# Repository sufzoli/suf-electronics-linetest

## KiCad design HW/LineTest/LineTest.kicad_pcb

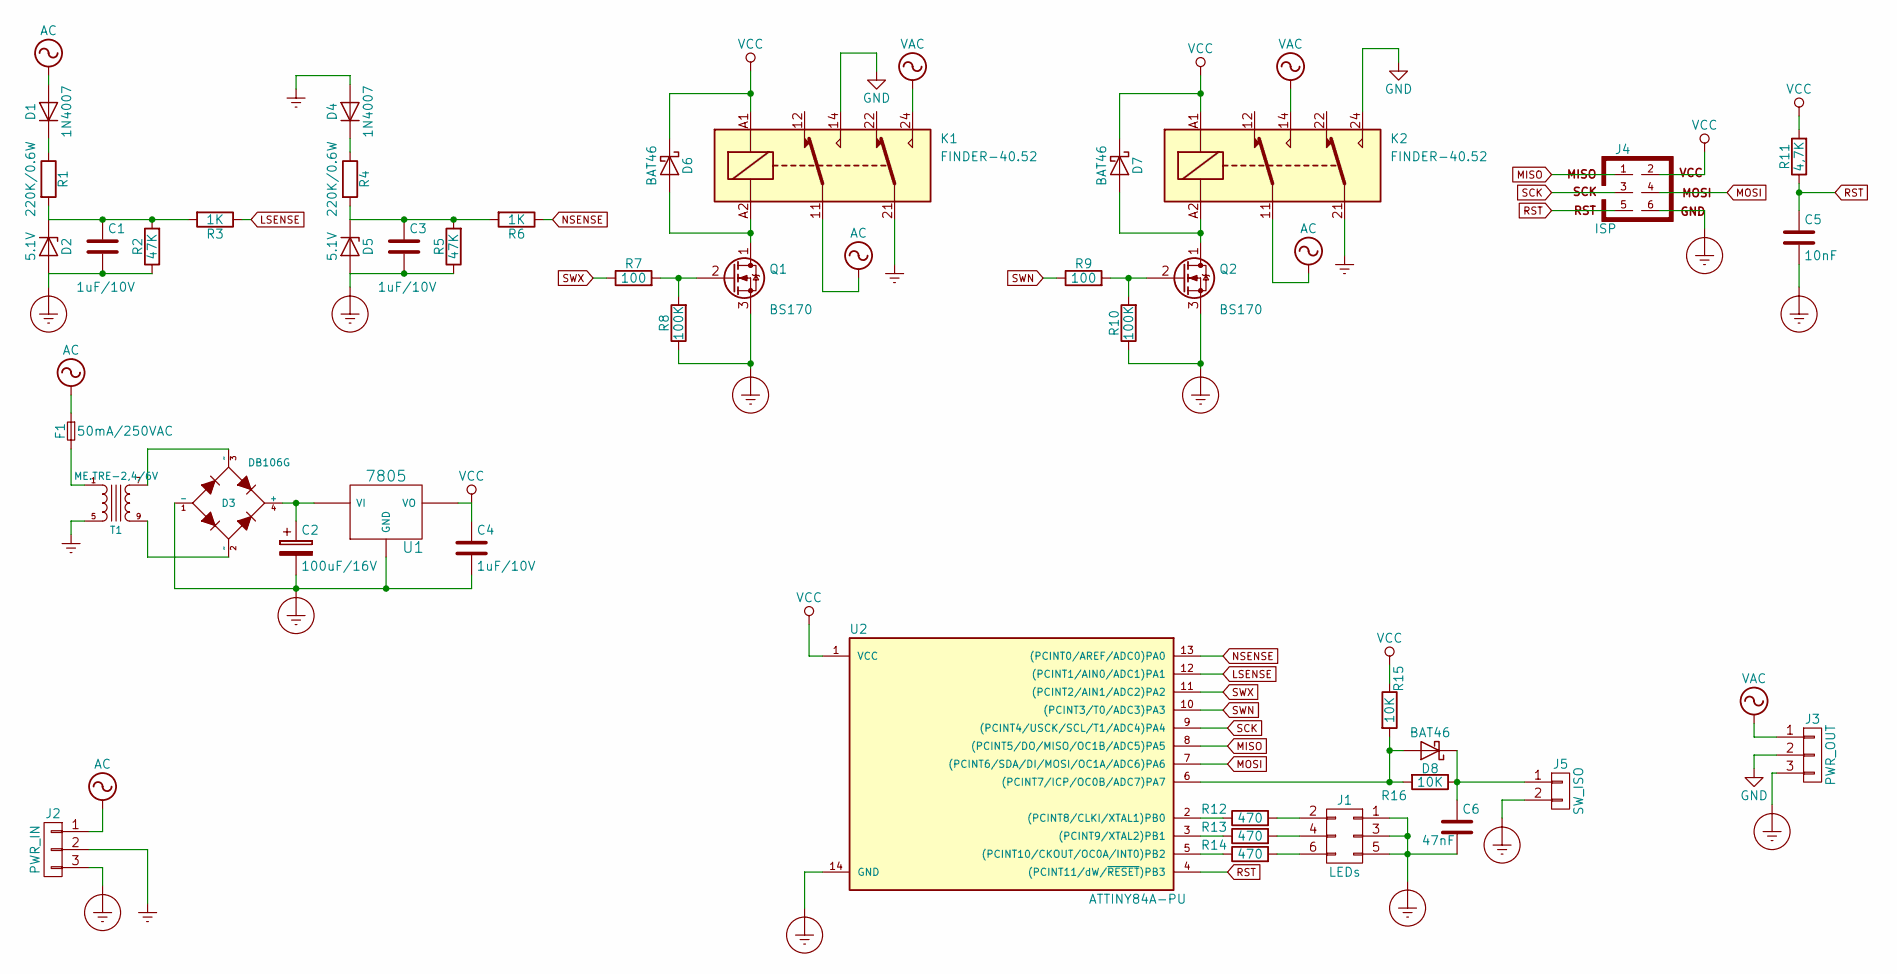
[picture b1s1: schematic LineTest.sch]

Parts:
C1, C3, C4: 1uF/10V; C_Disc_D3.0mm_W1.6mm_P2.50mm
C2: 100uF/16V; CP_Radial_D4.0mm_P2.00mm
C5: 10nF; C_Disc_D3.0mm_W1.6mm_P2.50mm
C6: 47nF; C_Disc_D3.0mm_W1.6mm_P2.50mm
D1, D4: 1N4007; D_DO-41_SOD81_P10.16mm_Horizontal
D2, D5: 5.1V; D_DO-35_SOD27_P7.62mm_Horizontal
D3: DB106G; DB-4
D6, D7, D8: BAT46; D_DO-35_SOD27_P7.62mm_Horizontal
F1: 50mA/250VAC; Fuseholder5x20_horiz_SemiClosed_Casing10x25mm
J1: LEDs; Pin_Header_Straight_2x03_Pitch2.54mm
J2: PWR_IN; CONN_NCW396-03S
J3: PWR_OUT; CONN_NCW396-03S
J4: ISP; Pin_Header_Straight_2x03_Pitch2.54mm
J5: SW_ISO; Pin_Header_Straight_1x02_Pitch2.54mm
K1, K2: FINDER-40.52; Relay_DPDT_Finder_40.52
Q1, Q2: BS170; TO-92_Molded_Wide
R1, R4: 220K/0.6W; R_Axial_DIN0207_L6.3mm_D2.5mm_P10.16mm_Horizontal
R2, R5: 47K; R_Axial_DIN0207_L6.3mm_D2.5mm_P10.16mm_Horizontal
R3, R6: 1K; R_Axial_DIN0207_L6.3mm_D2.5mm_P10.16mm_Horizontal
R7, R9: 100; R_Axial_DIN0207_L6.3mm_D2.5mm_P10.16mm_Horizontal
R8, R10: 100K; R_Axial_DIN0207_L6.3mm_D2.5mm_P10.16mm_Horizontal
R11: 4,7K; R_Axial_DIN0207_L6.3mm_D2.5mm_P10.16mm_Horizontal
R12, R13, R14: 470; R_Axial_DIN0207_L6.3mm_D2.5mm_P10.16mm_Horizontal
R15, R16: 10K; R_Axial_DIN0207_L6.3mm_D2.5mm_P10.16mm_Horizontal
T1: ME.TRE-2,4/6V; TR_ME.TRE-0,6
U1: 7805; TO-220-3_Vertical
U2: ATTINY84A-PU; DIP-14_W7.62mm

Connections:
AC: D1.2 (A), F1.1, J2.1, K1.11, K2.11
Earth: D4.2 (A), J2.2, K1.21, K2.21, T1.5
Earth_Protective: C1.2, C2.2, C3.2, C4.2, C5.2, C6.2, D2.2 (A), D3.1 (-), D5.2 (A), J1.1, J1.3, J1.5, J2.3, J3.3, J4.6, J5.2, Q1.3 (S), Q2.3 (S), R2.1, R5.1, R8.1, R10.1, U1.2 (GND), U2.14 (GND)
GND: J3.2, K1.14, K2.24
LSENSE: R3.1, U2.12 ((PCINT1/AIN0/ADC1)PA1)
MISO: J4.1, U2.8 ((PCINT5/DO/MISO/OC1B/ADC5)PA5)
MOSI: J4.4, U2.7 ((PCINT6/SDA/DI/MOSI/OC1A/ADC6)PA6)
NSENSE: R6.1, U2.13 ((PCINT0/AREF/ADC0)PA0)
unnamed: C1.1, D2.1 (K), R1.2, R2.2, R3.2
unnamed: C2.1, D3.4 (+), U1.1 (VI)
unnamed: C3.1, D5.1 (K), R4.2, R5.2, R6.2
unnamed: C6.1, D8.1 (K), J5.1, R16.1
unnamed: D1.1 (K), R1.1
unnamed: D3.2 (~~), T1.9
unnamed: D3.3 (~~), T1.7
unnamed: D4.1 (K), R4.1
unnamed: D6.2 (A), K1.A2, Q1.1 (D)
unnamed: D7.2 (A), K2.A2, Q2.1 (D)
unnamed: D8.2 (A), R15.2, R16.2, U2.6 ((PCINT7/ICP/OC0B/ADC7)PA7)
unnamed: F1.2, T1.1
unnamed: J1.2, R12.2
unnamed: J1.4, R13.2
unnamed: J1.6, R14.2
unnamed: Q1.2 (G), R7.2, R8.2
unnamed: Q2.2 (G), R9.2, R10.2
unnamed: R12.1, U2.2 ((PCINT8/CLKI/XTAL1)PB0)
unnamed: R13.1, U2.3 ((PCINT9/XTAL2)PB1)
unnamed: R14.1, U2.5 ((PCINT10/CKOUT/OC0A/INT0)PB2)
RST: C5.1, J4.5, R11.1, U2.4 ((PCINT11/dW/~RESET~)PB3)
SCK: J4.3, U2.9 ((PCINT4/USCK/SCL/T1/ADC4)PA4)
SWN: R9.1, U2.10 ((PCINT3/T0/ADC3)PA3)
SWX: R7.1, U2.11 ((PCINT2/AIN1/ADC2)PA2)
VAC: J3.1, K1.24, K2.14
VCC: C4.1, D6.1 (K), D7.1 (K), J4.2, K1.A1, K2.A1, R11.2, R15.1, U1.3 (VO), U2.1 (VCC)

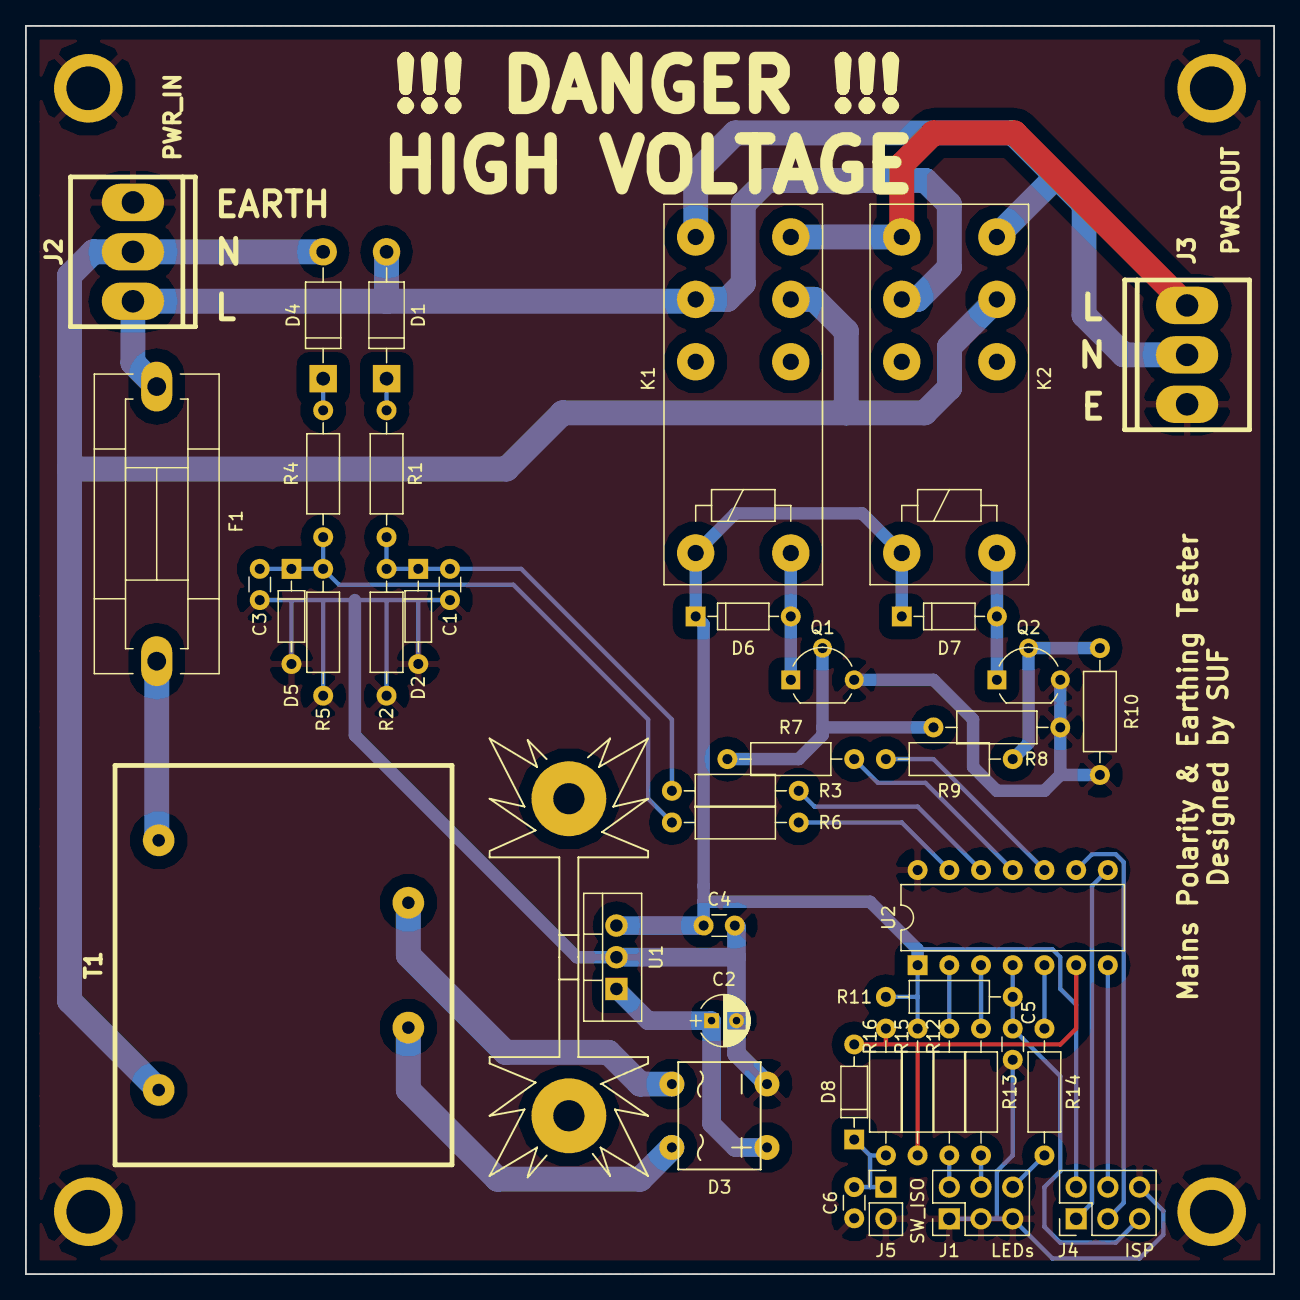
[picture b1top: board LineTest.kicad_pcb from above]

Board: 2 copper layers, 100.0 x 100.0 mm, 47 parts (0 on the bottom side), 34 nets.

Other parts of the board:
MNT_HOLE_3.5, MNT_HOLE_3.5#2, MNT_HOLE_3.5#3, MNT_HOLE_3.5#4: Val**; MNT_HOLE_3.5

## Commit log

2017-12-02 Almost finished software for V1 missing error handling for both sense high
2021-03-20 Add remaining data
